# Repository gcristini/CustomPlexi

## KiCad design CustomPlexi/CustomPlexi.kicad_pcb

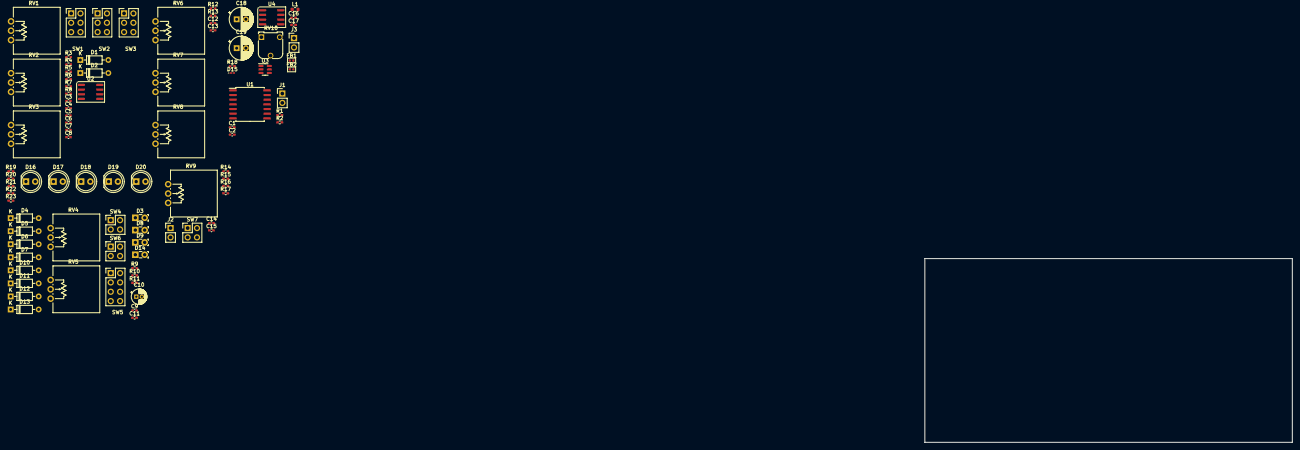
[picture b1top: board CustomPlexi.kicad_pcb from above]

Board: 2 copper layers, 100.0 x 50.0 mm, 89 parts (0 on the bottom side), 60 nets, no tracks yet.

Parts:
C1, C11: 330p; C_0402_1005Metric_Pad0.74x0.62mm_HandSolder
C2, C7: 220n; C_0402_1005Metric_Pad0.74x0.62mm_HandSolder
C3: 47n; C_0402_1005Metric_Pad0.74x0.62mm_HandSolder
C4, C5, C8: 1u; C_0402_1005Metric_Pad0.74x0.62mm_HandSolder
C6: 200n; C_0402_1005Metric_Pad0.74x0.62mm_HandSolder
C9: 33n; C_0402_1005Metric_Pad0.74x0.62mm_HandSolder
C10: C_Pol; CP_Radial_D4.0mm_P1.50mm
C12, C13: 470p; C_0402_1005Metric_Pad0.74x0.62mm_HandSolder
C14, C15: 470n; C_0402_1005Metric_Pad0.74x0.62mm_HandSolder
C16, C17: 22u; C_0402_1005Metric_Pad0.74x0.62mm_HandSolder
C18, C19: C_Polarized; CP_Radial_D6.3mm_P2.50mm
D1, D2, D6, D7, D12, D13: 1N4148; D_DO-35_SOD27_P7.62mm_Horizontal
D3, D8, D9, D14: Led Red; LED_SideEmitter_Rectangular_W4.5mm_H1.6mm
D4, D5, D10, D11: 1N34A; D_DO-35_SOD27_P7.62mm_Horizontal
D15: SS34; D_0201_0603Metric_Pad0.64x0.40mm_HandSolder
D16, D17, D18, D19, D20: LD271; LED_D5.0mm_IRGrey
FB1, FB2: FerriteBead_Small; Ferrite_0402_1005Metric
J1, J2, J3: Conn_01x02_Pin; PinHeader_1x02_P2.54mm_Vertical
L1: L; L_0603_1608Metric
R1, R5, R7, R8: 1k; R_0402_1005Metric_Pad0.72x0.64mm_HandSolder
R2: 1M; R_0402_1005Metric_Pad0.72x0.64mm_HandSolder
R3, R12, R13: 4.7k; R_0402_1005Metric_Pad0.72x0.64mm_HandSolder
R4: 51k; R_0402_1005Metric_Pad0.72x0.64mm_HandSolder
R6: 220; R_0402_1005Metric_Pad0.72x0.64mm_HandSolder
R9, R11: 2k; R_0402_1005Metric_Pad0.72x0.64mm_HandSolder
R10: 47k; R_0402_1005Metric_Pad0.72x0.64mm_HandSolder
R14, R15, R16, R17, R18: 22k; R_0402_1005Metric_Pad0.72x0.64mm_HandSolder
R19, R20, R21, R22, R23: 100k; R_0402_1005Metric_Pad0.72x0.64mm_HandSolder
RV1: 500k Log; Potentiometer_Vishay_148-149_Single_Vertical
RV2: 20k Lin; Potentiometer_Vishay_148-149_Single_Vertical
RV3: 100k Log; Potentiometer_Vishay_148-149_Single_Vertical
RV4: 100k Lin; Potentiometer_Vishay_148-149_Single_Vertical
RV5: 1M Log; Potentiometer_Vishay_148-149_Single_Vertical
RV6, RV7, RV8: 5k Log; Potentiometer_Vishay_148-149_Single_Vertical
RV9: 500k Lin; Potentiometer_Vishay_148-149_Single_Vertical
RV10: R_Potentiometer_Trim; Potentiometer_Runtron_RM-065_Vertical
SW1: Pedal Enable; SW_SPST_x3_PinHeader2.54mm
SW2: TS_Enable; SW_SPST_x3_PinHeader2.54mm
SW3: Preamp Enable; SW_SPST_x3_PinHeader2.54mm
SW4: Clipping Type; SW_SP3T_PinHeader2.54mm
SW5: Plexi Channel Select; SW_SPST_x4_PinHeader2.54mm
SW6: Diode Select; SW_SP3T_PinHeader2.54mm
SW7: Boost Enable/Disable; SW_SPST_x2_PinHeader2.54mm
U1: TL074; SOIC-14W_7.5x9mm_P1.27mm
U2: RC4558; SOIC-8_3.9x4.9mm_P1.27mm
U3: MT3608; SOT-23-6
U4: ICL7662; SOIC-8_3.9x4.9mm_P1.27mm

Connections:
+9V: C16.2, J3.1, L1.1, SW1.2, SW3.2, SW5.2, SW7.2, U3.4 (EN), U3.5 (IN)
+12V: C17.2, D15.2 (A), FB1.1, RV10.1, U4.8 (V+)
-12V: C19.2, FB2.1, U4.5 (VOUT)
/Boost/Boost: R15.2, RV9.2, RV9.3, SW7.1
/Plexi/Crunch: C11.1, D3.2 (A), D4.1 (K), D5.2 (A), D6.1 (K), D7.2 (A), D8.1 (K), R9.2, RV4.2, RV4.3, RV5.2, RV5.3, U1.2 (-)
/Preamp/TS_Gain: C5.2, D1.2 (A), D2.1 (K), R5.2, RV1.1, RV1.2, U2.1
/Preamp/TS_Tone: C7.2, RV2.2
/Preamp/TS_Volume: RV3.2, SW3.1
/Tone Stack/Crunch Level: RV8.2, SW5.1
/Tone Stack/Lead Level: RV7.2, SW5.3
/Tone Stack/Tone: C12.2, R13.1, RV6.2, RV6.3, U1.13 (-)
Buffer_Out/Preamp_In: U1.6 (-), U1.7
GND: C1.2, C6.1, C10.2, C16.1, C17.1, C19.1, D16.1 (K), D17.1 (K), D18.1 (K), D19.1 (K), D20.1 (K), J1.2, J2.2, J3.2, R2.1, R3.2, R6.2, R10.1, R17.1, R18.1, RV3.3, RV7.3, RV8.3, U1.10 (+), U1.12 (+), U3.2 (GND), U4.3 (GND)
Guitar_In: J1.1, R1.1
unnamed: C1.1, C2.1, R1.2
unnamed: C3.1, R3.1
unnamed: C4.1, SW2.1
unnamed: C7.1, R6.1
unnamed: C8.1, R8.1
unnamed: C8.2, R7.1, U2.7
unnamed: C10.1, R9.1
unnamed: C12.1, R12.2
unnamed: C13.1, RV6.1
unnamed: C13.2, R13.2, U1.14
unnamed: C14.1, R14.2
unnamed: C15.2, R16.2, U1.8
unnamed: C3.2, C5.1, D1.1 (K), D2.2 (A), R4.2, U2.2 (-)
unnamed: D3.1 (K), D9.2 (A)
unnamed: D10.2 (A), D11.1 (K), SW4.2, SW6.1
unnamed: D4.2 (A), D10.1 (K), SW4.1
unnamed: D5.1 (K), D11.2 (A)
unnamed: D12.2 (A), D13.1 (K), SW6.2
unnamed: D6.2 (A), D12.1 (K)
unnamed: D7.1 (K), D13.2 (A)
unnamed: D9.1 (K), D14.2 (A), SW6.4
unnamed: D8.2 (A), D14.1 (K)
unnamed: D15.1 (K), L1.2, U3.1 (SW)
unnamed: D16.2 (A), R19.2
unnamed: D17.2 (A), R20.2
unnamed: D18.2 (A), R21.2
unnamed: D19.2 (A), R22.2
unnamed: D20.2 (A), R23.2
unnamed: R4.1, RV1.3
unnamed: R8.2, RV3.1
unnamed: R19.1, SW1.1
unnamed: RV9.1, SW7.3
unnamed: SW2.3, SW3.3
unnamed: C9.2, R10.2, U1.3 (+)
unnamed: C2.2, R2.2, U1.5 (+)
unnamed: C14.2, C15.1, R15.1, U1.9 (-)
unnamed: FB1.2, U1.4 (V+), U2.8 (V+)
unnamed: FB2.2, U1.11 (V-), U2.4 (V-)
unnamed: C4.2, U2.3 (+)
unnamed: C6.2, R5.1, RV2.3, U2.5 (+)
unnamed: R7.2, RV2.1, U2.6 (-)
unnamed: R18.2, RV10.3, U3.3 (FB)
unnamed: C18.1, U4.2 (CAP+)
unnamed: C18.2, U4.4 (CAP-)
Plexi_Out/Tone_In: C11.2, R11.1, R12.1, SW6.3, U1.1
To_Amp: J2.1, R16.1, R17.2

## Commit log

2023-05-30 Signal chain ok except separated volumes
2023-05-30 added leds
2023-05-30 crunch and leadh channel has separated level control
2023-05-30 some changes
2023-05-31 switches reviewed
2023-06-20 input dcdc and negative voltage converter. To decide values
2023-07-11 deleted tone stack
2023-07-11 Full ts808
2023-07-11 changed refdes
2023-07-14 drawing update
